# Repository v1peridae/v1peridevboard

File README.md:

# v1peridevboard

<p align="center">⛧°。 ⋆༺♱༻⋆。 °⛧ neo-tribal themed devboard powered by the rp2040 ⛧°。 ⋆༺♱༻⋆。 °⛧</p>
<br>

<br>

## what is this lou?

do you own a raspberry pi pico? it's just about the same thing! 

i haven't quite yet figured out what i'm going to do with it lol but i just wanted something cool :P

## where'd ya make it?

on kicad! i spent about 8 hours making it (routing was THE hardest). 

learn how it was made in <a href="/JOURNAL.md"> journal.md </a>:)

## schematics

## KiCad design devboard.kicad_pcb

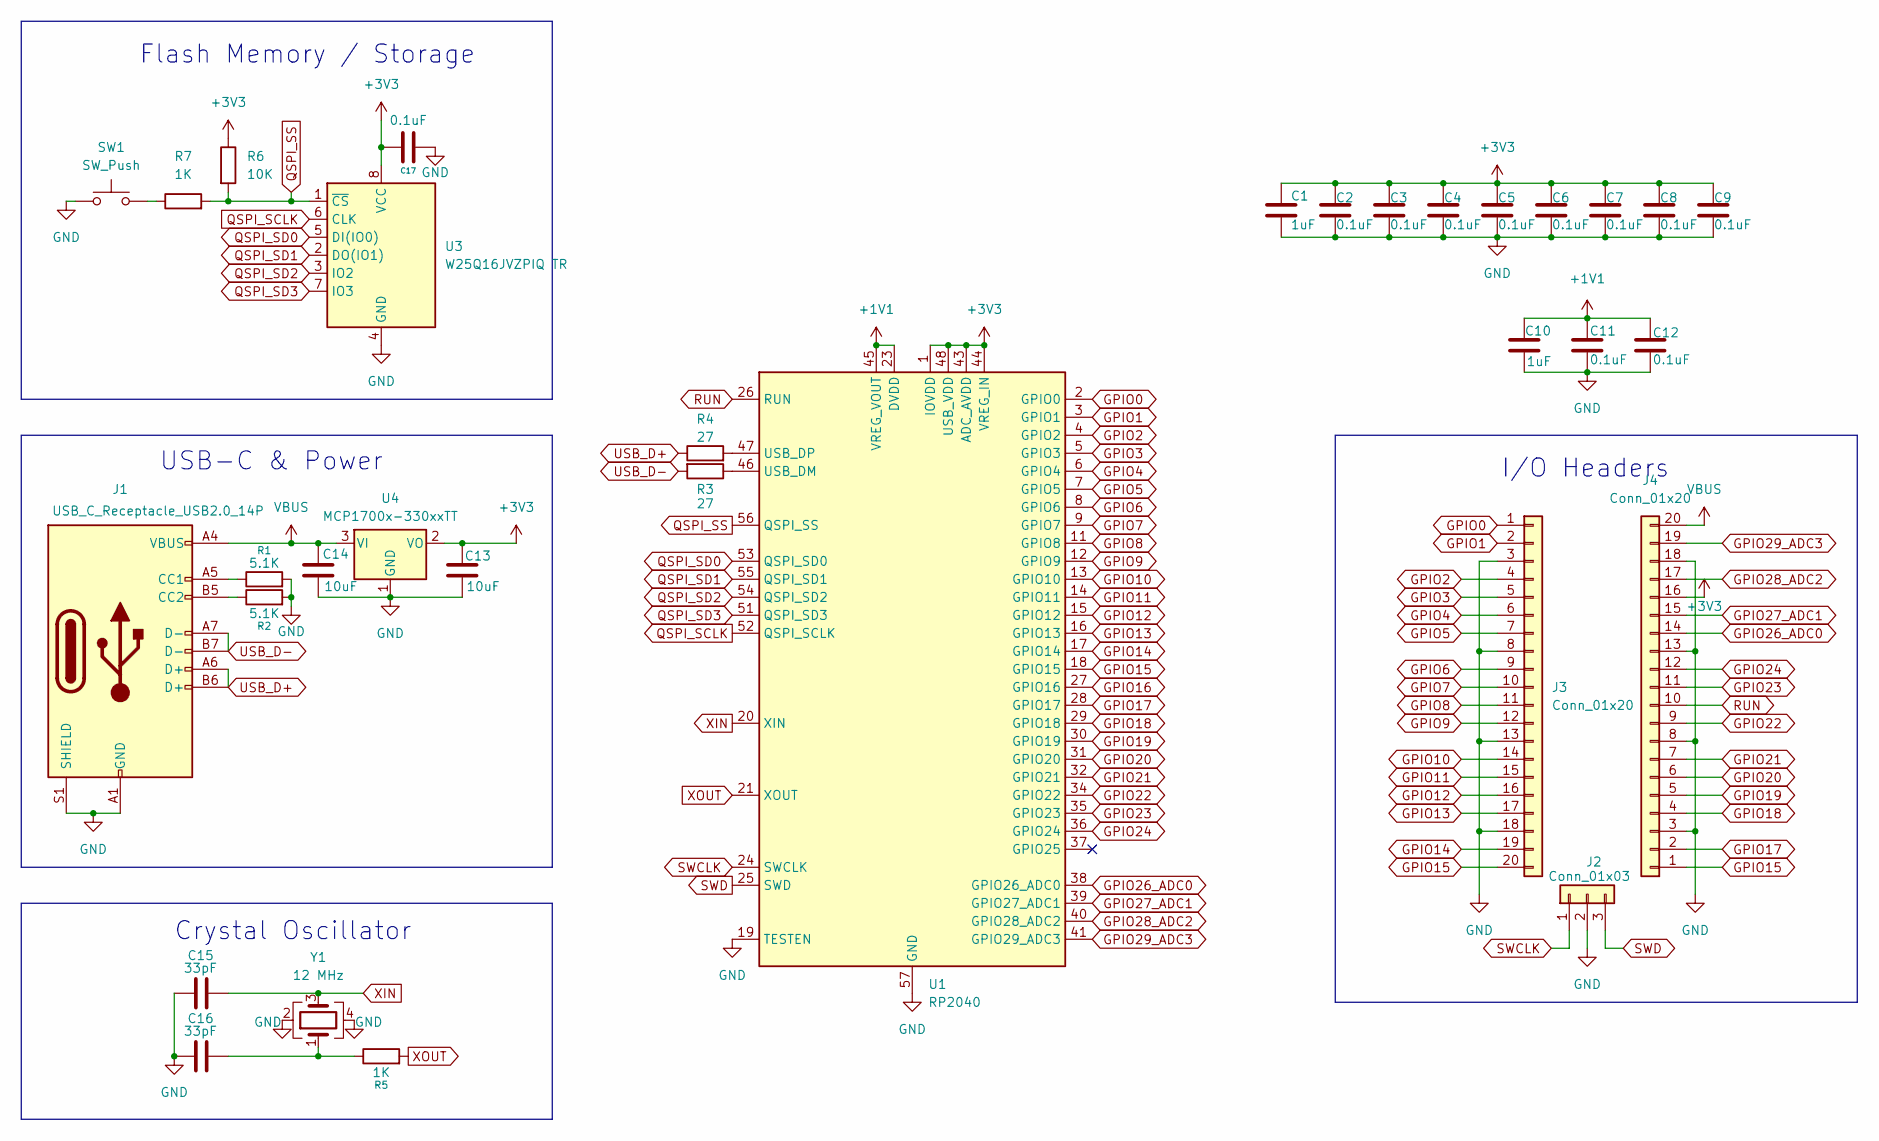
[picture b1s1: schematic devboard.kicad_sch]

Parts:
C1, C10: 1uF; C_0402_1005Metric
C2, C3, C4, C5, C6, C7, C8, C9, C11, C12, C17: 0.1uF; C_0402_1005Metric
C13, C14: 10uF; C_0603_1608Metric
C15, C16: 33pF; C_0402_1005Metric
J1: USB_C_Receptacle_USB2.0_14P; USB_C_Receptacle_HRO_TYPE-C-31-M-12
J2: Conn_01x03; PinHeader_1x03_P2.54mm_Vertical
J3, J4: Conn_01x20; PinHeader_1x20_P2.54mm_Vertical
R1, R2: 5.1K; R_0402_1005Metric
R3, R4: 27; R_0402_1005Metric
R5, R7: 1K; R_0402_1005Metric
R6: 10K; R_0402_1005Metric
SW1: SW_Push; SW_Push_SPST_NO_Alps_SKRK
U1: RP2040; QFN-56-1EP_7x7mm_P0.4mm_EP3.2x3.2mm
U3: W25Q16JVZPIQ TR; Winbond_USON-8-1EP_3x2mm_P0.5mm_EP0.2x1.6mm
U4: MCP1700x-330xxTT; SOT-23
Y1: 12 MHz; Crystal_SMD_3225-4Pin_3.2x2.5mm

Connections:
+1V1: C10.1, C11.1, C12.1, U1.23 (DVDD), U1.45 (VREG_VOUT), U1.50 (DVDD)
+3V3: C1.1, C2.1, C3.1, C4.1, C5.1, C6.1, C7.1, C8.1, C9.1, C13.1, C17.2, J4.16, R6.1, U1.1 (IOVDD), U1.10 (IOVDD), U1.22 (IOVDD), U1.33 (IOVDD), U1.42 (IOVDD), U1.43 (ADC_AVDD), U1.44 (VREG_IN), U1.48 (USB_VDD), U1.49 (IOVDD), U3.8 (VCC), U4.2 (VO); also elsewhere on the board
GND: C1.2, C2.2, C3.2, C4.2, C5.2, C6.2, C7.2, C8.2, C9.2, C10.2, C11.2, C12.2, C13.2, C14.2, C15.2, C16.2, C17.1, J1.A1 (GND), J1.A12 (GND), J1.B1 (GND), J1.B12 (GND), J1.S1 (SHIELD), J2.2, J3.3, J3.8, J3.13, J3.18, J4.3, J4.8, J4.13, J4.18, R1.2, R2.2, SW1.1, U1.19 (TESTEN), U1.57 (GND), U3.4 (GND), U4.1 (GND), Y1.2, Y1.4; also elsewhere on the board
GPIO0: J3.1, U1.2 (GPIO0)
GPIO1: J3.2, U1.3 (GPIO1)
GPIO2: J3.4, U1.4 (GPIO2)
GPIO3: J3.5, U1.5 (GPIO3)
GPIO4: J3.6, U1.6 (GPIO4)
GPIO5: J3.7, U1.7 (GPIO5)
GPIO6: J3.9, U1.8 (GPIO6)
GPIO7: J3.10, U1.9 (GPIO7)
GPIO8: J3.11, U1.11 (GPIO8)
GPIO9: J3.12, U1.12 (GPIO9)
GPIO10: J3.14, U1.13 (GPIO10)
GPIO11: J3.15, U1.14 (GPIO11)
GPIO12: J3.16, U1.15 (GPIO12)
GPIO13: J3.17, U1.16 (GPIO13)
GPIO14: J3.19, U1.17 (GPIO14)
GPIO17: J4.2, U1.28 (GPIO17)
GPIO18: J4.4, U1.29 (GPIO18)
GPIO19: J4.5, U1.30 (GPIO19)
GPIO20: J4.6, U1.31 (GPIO20)
GPIO21: J4.7, U1.32 (GPIO21)
GPIO22: J4.9, U1.34 (GPIO22)
GPIO23: J4.11, U1.35 (GPIO23)
GPIO24: J4.12, U1.36 (GPIO24)
GPIO26_ADC0: J4.14, U1.38 (GPIO26_ADC0)
GPIO27_ADC1: J4.15, U1.39 (GPIO27_ADC1)
GPIO28_ADC2: J4.17, U1.40 (GPIO28_ADC2)
GPIO29_ADC3: J4.19, U1.41 (GPIO29_ADC3)
unnamed: C16.1, R5.1, Y1.1
unnamed: J1.A5 (CC1), R1.1
unnamed: J1.B5 (CC2), R2.1
unnamed: R7.1, SW1.2
unnamed: R3.1, U1.46 (USB_DM)
unnamed: R4.2, U1.47 (USB_DP)
QSPI_SCLK: U1.52 (QSPI_SCLK), U3.6 (CLK)
QSPI_SD0: U1.53 (QSPI_SD0), U3.5 (DI(IO0))
QSPI_SD1: U1.55 (QSPI_SD1), U3.2 (DO(IO1))
QSPI_SD2: U1.54 (QSPI_SD2), U3.3 (IO2)
QSPI_SD3: U1.51 (QSPI_SD3), U3.7 (IO3)
QSPI_SS: R6.2, R7.2, U1.56 (QSPI_SS), U3.1 (~CS)
RUN: J4.10, U1.26 (RUN)
SWCLK: J2.1, U1.24 (SWCLK)
SWD: J2.3, U1.25 (SWD)
USB_D+: J1.A6 (D+), J1.B6 (D+), R4.1
USB_D-: J1.A7 (D-), J1.B7 (D-), R3.2
VBUS: C14.1, J1.A4 (VBUS), J1.A9 (VBUS), J1.B4 (VBUS), J1.B9 (VBUS), J4.20, U4.3 (VI); also elsewhere on the board
XIN: C15.1, U1.20 (XIN), Y1.3
XOUT: R5.2, U1.21 (XOUT)

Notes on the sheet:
Crystal Oscillator
I/O Headers
USB-C & Power
Flash Memory / Storage

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
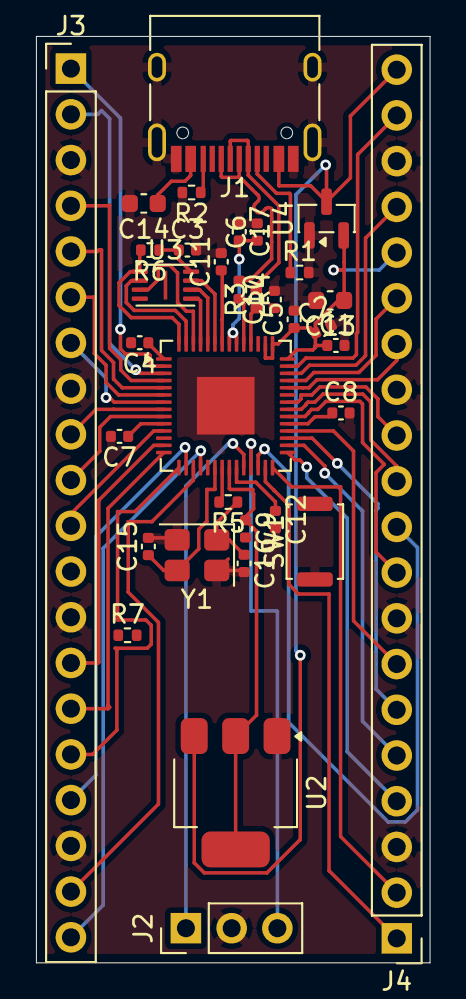
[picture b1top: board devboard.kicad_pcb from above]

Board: 2 copper layers, 21.9 x 51.5 mm, 34 parts (0 on the bottom side), 52 nets.

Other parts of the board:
U2: NCP1117-3.3_SOT223; SOT-223-3_TabPin2

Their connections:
+3V3: U2.2 (VO); also elsewhere on the board
GND: U2.1 (GND); also elsewhere on the board
VBUS: U2.3 (VI); also elsewhere on the board

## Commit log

2025-10-16 i did this on iwindows...moving to mac now that i dont need hackatime :P
2025-10-16 change file arrangement
2025-10-17 finished schematics...next is footprints :0
2025-10-19 layout is my biggest opp </3
2025-10-19 some routing (help me)
2025-10-26 routing done. i am crashing out over drc lol
2025-11-07 done! added finishing touches
2025-11-07 add bom
2025-11-12 add schematics png
